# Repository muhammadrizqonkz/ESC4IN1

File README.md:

# ESC4IN1

Dokumentasi proyek capstone ESC 4-in-1: desain PCB, simulasi, dan pengujian motor.

## Isi repositori

| Folder | Isi |
| --- | --- |
| [PCBDesign](PCBDesign/) | Desain PCB KiCad dan model 3D |
| [Simulation](Simulation/) | Model dan hasil simulasi |
| [MotorTest](MotorTest/) | Foto pengukuran dan pengujian |

## PCBDesign

- [Skematik](PCBDesign/ESC_4in1.kicad_sch)
- [Layout PCB](PCBDesign/ESC_4in1.kicad_pcb)
- [Project KiCad](PCBDesign/ESC_4in1.kicad_pro)
- [Model 3D (STEP)](PCBDesign/ESC.step)
- [Render 3D](PCBDesign/ESC3D.png)

## Simulation

- [Model simulasi](Simulation/ModelSimulasi.png)
- [Hasil simulasi](Simulation/HasilSimulasi.jpeg)

## MotorTest

- [Pengukuran induktansi](MotorTest/InductanceMeasure.jpeg)
- [Pengukuran resistansi](MotorTest/ResistanceMeasure.jpeg)
- [Kamera termal ESC](MotorTest/ThermalCamESC.jpeg)

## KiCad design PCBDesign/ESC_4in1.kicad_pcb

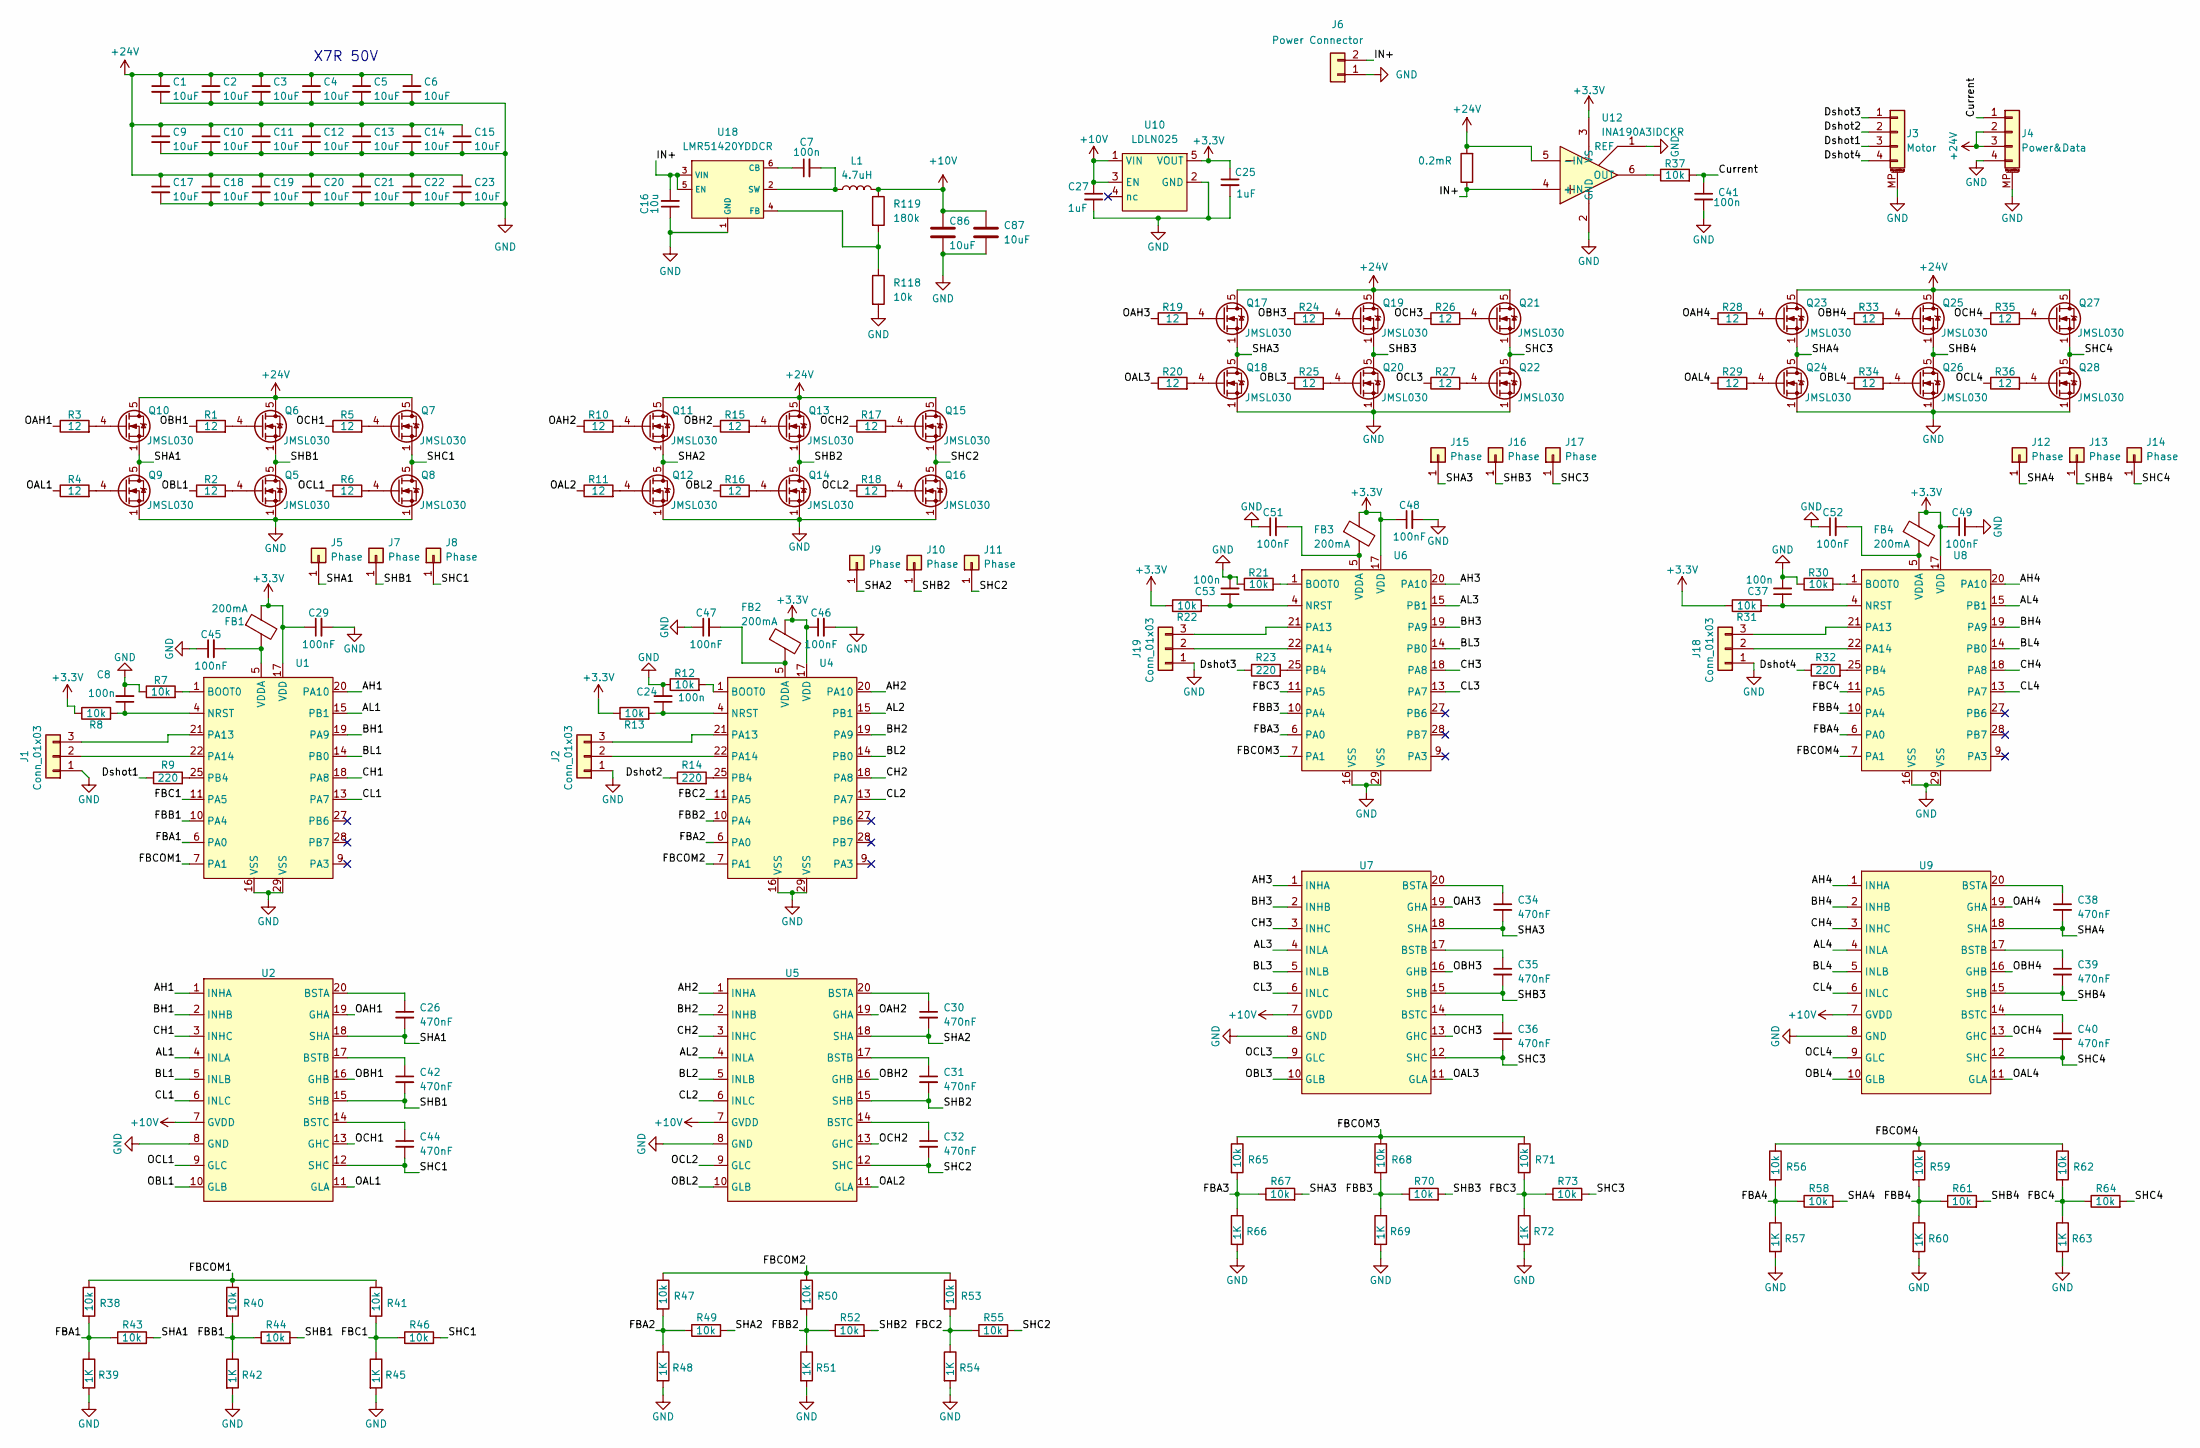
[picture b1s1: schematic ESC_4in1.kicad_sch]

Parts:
C1, C2, C3, C4, C5, C6, C9, C10, C11, C12, C13, C14, C15, C17, C18, C19, C20, C21, C22, C23: 10uF; C_1206_3216Metric_Pad1.33x1.80mm_HandSolder
C7: 100n; C_0603_1608Metric_Pad1.08x0.95mm_HandSolder
C8, C24, C37, C41, C53: 100n; C_0402_1005Metric_Pad0.74x0.62mm_HandSolder
C16: 10u; C_0603_1608Metric_Pad1.08x0.95mm_HandSolder
C25, C27: 1uF; C_0603_1608Metric_Pad1.08x0.95mm_HandSolder
C26, C30, C31, C32, C34, C35, C36, C38, C39, C40, C42, C44: 470nF; C_0603_1608Metric_Pad1.08x0.95mm_HandSolder
C29, C45, C46, C47, C48, C49, C51, C52: 100nF; C_01005_0402Metric_Pad0.57x0.30mm_HandSolder
C86, C87: 10uF; C_0603_1608Metric; LCSC C2762594
FB1, FB2, FB3, FB4: 200mA; R_0201_0603Metric_Pad0.64x0.40mm_HandSolder
J1, J2, J19: Conn_01x03; PinHeader_1x03_P2.54mm_Horizontal
J3: Motor; JST_SH_SM04B-SRSS-TB_1x04-1MP_P1.00mm_Horizontal
J4: Power&Data; JST_SH_SM04B-SRSS-TB_1x04-1MP_P1.00mm_Horizontal
J5, J7, J8, J9, J10, J11, J12, J13, J14, J15, J16, J17: Phase; motorterminal
J6: Power Connector; AMASS_XT30PW-M
J18: Conn_01x03; PinHeader_1x03_P2.54mm_Vertical_SMD_Pin1Left
L1: 4.7uH; SPM3012
Q5, Q6, Q7, Q8, Q9, Q10, Q11, Q12, Q13, Q14, Q15, Q16, Q17, Q18, Q19, Q20, Q21, Q22, Q23, Q24, Q25, Q26, Q27, Q28: JMSL030; Vishay_PowerPAK_1212-8_Single
R1, R2, R3, R4, R5, R6, R10, R11, R15, R16, R17, R18, R19, R20, R24, R25, R26, R27, R28, R29, R33, R34, R35, R36: 12; R_0603_1608Metric_Pad0.98x0.95mm_HandSolder
R7, R8, R12, R13, R21, R22, R30, R31, R38, R40, R41, R43, R44, R46, R47, R49, R50, R52, R53, R55, R56, R58, R59, R61, R62, R64, R65, R67, R68, R70, R71, R73: 10k; R_0603_1608Metric_Pad0.98x0.95mm_HandSolder
R9, R14, R23, R32: 220; R_0603_1608Metric_Pad0.98x0.95mm_HandSolder
R37: 10k; R_0402_1005Metric_Pad0.72x0.64mm_HandSolder
R39, R42, R45, R48, R51, R54, R57, R60, R63, R66, R69, R72: 1K; R_0603_1608Metric_Pad0.98x0.95mm_HandSolder
R118: 10k; R_0402_1005Metric_Pad0.72x0.64mm_HandSolder; LCSC C106225
R119: 180k; R_0402_1005Metric_Pad0.72x0.64mm_HandSolder; LCSC C423759
Rsense1: 0.2mR; R_2512_6332Metric; LCSC C695806
U1, U4, U6, U8: QFN-28-1EP_4x4mm_P0.4mm_EP2.4x2.4mm
U2, U5, U7, U9: TSSOP-20_4.4x6.5mm_P0.65mm
U10: LDLN025; SOT-23-5_HandSoldering
U12: INA190A3IDCKR; SOT-363_SC-70-6; LCSC C2058245
U18: LMR51420YDDCR; SOT-23-6_Handsoldering; LCSC C7296200

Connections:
+3.3V: C25.1, C29.1, C46.1, C48.1, C49.1, FB1.1, FB2.1, FB3.1, FB4.1, R8.1, R13.1, R22.1, R31.1, U1.17 (VDD), U4.17 (VDD), U6.17 (VDD), U8.17 (VDD), U10.5 (VOUT), U12.3 (VS)
+10V: C27.1, C86.1, C87.1, L1.1, R119.1, U2.7 (GVDD), U5.7 (GVDD), U7.7 (GVDD), U9.7 (GVDD), U10.1 (VIN), U10.3 (EN)
+24V: C1.1, C2.1, C3.1, C4.1, C5.1, C6.1, C9.1, C10.1, C11.1, C12.1, C13.1, C14.1, C15.1, C17.1, C18.1, C19.1, C20.1, C21.1, C22.1, C23.1, J4.2, J4.3, Q6.5 (D), Q7.5 (D), Q10.5 (D), Q11.5 (D), Q13.5 (D), Q15.5 (D), Q17.5 (D), Q19.5 (D), Q21.5 (D), Q23.5 (D), Q25.5 (D), Q27.5 (D), Rsense1.2, U12.5 (-IN)
/AH1: U1.20 (PA10), U2.1 (INHA)
/AH2: U4.20 (PA10), U5.1 (INHA)
/AH3: U6.20 (PA10), U7.1 (INHA)
/AH4: U8.20 (PA10), U9.1 (INHA)
/AL1: U1.15 (PB1), U2.4 (INLA)
/AL2: U4.15 (PB1), U5.4 (INLA)
/AL3: U6.15 (PB1), U7.4 (INLA)
/AL4: U8.15 (PB1), U9.4 (INLA)
/BH1: U1.19 (PA9), U2.2 (INHB)
/BH2: U4.19 (PA9), U5.2 (INHB)
/BH3: U6.19 (PA9), U7.2 (INHB)
/BH4: U8.19 (PA9), U9.2 (INHB)
/BL1: U1.14 (PB0), U2.5 (INLB)
/BL2: U4.14 (PB0), U5.5 (INLB)
/BL3: U6.14 (PB0), U7.5 (INLB)
/BL4: U8.14 (PB0), U9.5 (INLB)
/CH1: U1.18 (PA8), U2.3 (INHC)
/CH2: U4.18 (PA8), U5.3 (INHC)
/CH3: U6.18 (PA8), U7.3 (INHC)
/CH4: U8.18 (PA8), U9.3 (INHC)
/CL1: U1.13 (PA7), U2.6 (INLC)
/CL2: U4.13 (PA7), U5.6 (INLC)
/CL3: U6.13 (PA7), U7.6 (INLC)
/CL4: U8.13 (PA7), U9.6 (INLC)
/Current: C41.1, J4.1, R37.2
/Dshot1: J3.3, R9.1
/Dshot2: J3.2, R14.1
/Dshot3: J3.1, R23.1
/Dshot4: J3.4, R32.1
/FBA1: R38.2, R39.1, R43.1, U1.6 (PA0)
/FBA2: R47.2, R48.1, R49.1, U4.6 (PA0)
/FBA3: R65.2, R66.1, R67.1, U6.6 (PA0)
/FBA4: R56.2, R57.1, R58.1, U8.6 (PA0)
/FBB1: R40.2, R42.1, R44.1, U1.10 (PA4)
/FBB2: R50.2, R51.1, R52.1, U4.10 (PA4)
/FBB3: R68.2, R69.1, R70.1, U6.10 (PA4)
/FBB4: R59.2, R60.1, R61.1, U8.10 (PA4)
/FBC1: R41.2, R45.1, R46.1, U1.11 (PA5)
/FBC2: R53.2, R54.1, R55.1, U4.11 (PA5)
/FBC3: R71.2, R72.1, R73.1, U6.11 (PA5)
/FBC4: R62.2, R63.1, R64.1, U8.11 (PA5)
/FBCOM1: R38.1, R40.1, R41.1, U1.7 (PA1)
/FBCOM2: R47.1, R50.1, R53.1, U4.7 (PA1)
/FBCOM3: R65.1, R68.1, R71.1, U6.7 (PA1)
/FBCOM4: R56.1, R59.1, R62.1, U8.7 (PA1)
/IN+: C16.2, J6.2, Rsense1.1, U12.4 (+IN), U18.3 (VIN), U18.5 (EN)
/OAH1: R3.1, U2.19 (GHA)
/OAH2: R10.1, U5.19 (GHA)
/OAH3: R19.1, U7.19 (GHA)
/OAH4: R28.1, U9.19 (GHA)
/OAL1: R4.1, U2.11 (GLA)
/OAL2: R11.1, U5.11 (GLA)
/OAL3: R20.1, U7.11 (GLA)
/OAL4: R29.1, U9.11 (GLA)
/OBH1: R1.1, U2.16 (GHB)
/OBH2: R15.1, U5.16 (GHB)
/OBH3: R24.1, U7.16 (GHB)
/OBH4: R33.1, U9.16 (GHB)
/OBL1: R2.1, U2.10 (GLB)
/OBL2: R16.1, U5.10 (GLB)
/OBL3: R25.1, U7.10 (GLB)
/OBL4: R34.1, U9.10 (GLB)
/OCH1: R5.1, U2.13 (GHC)
/OCH2: R17.1, U5.13 (GHC)
/OCH3: R26.1, U7.13 (GHC)
/OCH4: R35.1, U9.13 (GHC)
/OCL1: R6.1, U2.9 (GLC)
/OCL2: R18.1, U5.9 (GLC)
/OCL3: R27.1, U7.9 (GLC)
/OCL4: R36.1, U9.9 (GLC)
/SHA1: C26.2, J5.1 (Pin_1_1), Q9.5 (D), Q10.1 (S), Q10.2 (S), Q10.3 (S), R43.2, U2.18 (SHA)
/SHA2: C30.2, J9.1 (Pin_1_1), Q11.1 (S), Q11.2 (S), Q11.3 (S), Q12.5 (D), R49.2, U5.18 (SHA)
/SHA3: C34.2, J15.1 (Pin_1_1), Q17.1 (S), Q17.2 (S), Q17.3 (S), Q18.5 (D), R67.2, U7.18 (SHA)
/SHA4: C38.2, J12.1 (Pin_1_1), Q23.1 (S), Q23.2 (S), Q23.3 (S), Q24.5 (D), R58.2, U9.18 (SHA); also elsewhere on the board
/SHB1: C42.2, J7.1 (Pin_1_1), Q5.5 (D), Q6.1 (S), Q6.2 (S), Q6.3 (S), R44.2, U2.15 (SHB)
/SHB2: C31.2, J10.1 (Pin_1_1), Q13.1 (S), Q13.2 (S), Q13.3 (S), Q14.5 (D), R52.2, U5.15 (SHB)
/SHB3: C35.2, J16.1 (Pin_1_1), Q19.1 (S), Q19.2 (S), Q19.3 (S), Q20.5 (D), R70.2, U7.15 (SHB)
/SHB4: C39.2, J13.1 (Pin_1_1), Q25.1 (S), Q25.2 (S), Q25.3 (S), Q26.5 (D), R61.2, U9.15 (SHB)
/SHC1: C44.2, J8.1 (Pin_1_1), Q7.1 (S), Q7.2 (S), Q7.3 (S), Q8.5 (D), R46.2, U2.12 (SHC)
/SHC2: C32.2, J11.1 (Pin_1_1), Q15.1 (S), Q15.2 (S), Q15.3 (S), Q16.5 (D), R55.2, U5.12 (SHC)
/SHC3: C36.2, J17.1 (Pin_1_1), Q21.1 (S), Q21.2 (S), Q21.3 (S), Q22.5 (D), R73.2, U7.12 (SHC)
/SHC4: C40.2, J14.1 (Pin_1_1), Q27.1 (S), Q27.2 (S), Q27.3 (S), Q28.5 (D), R64.2, U9.12 (SHC)
GND: C1.2, C2.2, C3.2, C4.2, C5.2, C6.2, C8.2, C9.2, C10.2, C11.2, C12.2, C13.2, C14.2, C15.2, C16.1, C17.2, C18.2, C19.2, C20.2, C21.2, C22.2, C23.2, C24.2, C25.2, C27.2, C29.2, C37.2, C41.2, C45.1, C46.2, C47.1, C48.2, C49.2, C51.1, C52.1, C53.2, C86.2, C87.2, J1.1, J2.1, J3.MP (MountPin), J4.4, J4.MP (MountPin), J6.1, J18.1, J19.1, Q5.1 (S), Q5.2 (S), Q5.3 (S), Q8.1 (S), Q8.2 (S), Q8.3 (S), Q9.1 (S), Q9.2 (S), Q9.3 (S), Q12.1 (S), Q12.2 (S), Q12.3 (S), Q14.1 (S), Q14.2 (S), Q14.3 (S), Q16.1 (S), Q16.2 (S), Q16.3 (S), Q18.1 (S), Q18.2 (S), Q18.3 (S), Q20.1 (S), Q20.2 (S), Q20.3 (S), Q22.1 (S), Q22.2 (S), Q22.3 (S), Q24.1 (S), Q24.2 (S), Q24.3 (S), Q26.1 (S), Q26.2 (S), Q26.3 (S), Q28.1 (S), Q28.2 (S), Q28.3 (S), R7.1, R12.1, R21.1, R30.1, R39.2, R42.2, R45.2, R48.2, R51.2, R54.2, R57.2, R60.2, R63.2, R66.2, R69.2, R72.2, R118.2, U1.16 (VSS), U1.29 (VSS), U2.8 (GND), U4.16 (VSS), U4.29 (VSS), U5.8 (GND), U6.16 (VSS), U6.29 (VSS), U7.8 (GND), U8.16 (VSS), U8.29 (VSS), U9.8 (GND), U10.2 (GND), U12.1 (REF), U12.2 (GND), U18.1 (GND)
unnamed: J1.2, U1.22 (PA14)
unnamed: J1.3, U1.21 (PA13)
unnamed: J2.2, U4.22 (PA14)
unnamed: J2.3, U4.21 (PA13)
unnamed: J18.2, U8.22 (PA14)
unnamed: J18.3, U8.21 (PA13)
unnamed: J19.2, U6.22 (PA14)
unnamed: J19.3, U6.21 (PA13)
unnamed: Q5.4 (G), R2.2
unnamed: Q6.4 (G), R1.2
unnamed: Q7.4 (G), R5.2
unnamed: Q8.4 (G), R6.2
unnamed: Q9.4 (G), R4.2
unnamed: Q10.4 (G), R3.2
unnamed: Q11.4 (G), R10.2
unnamed: Q12.4 (G), R11.2
unnamed: Q13.4 (G), R15.2
unnamed: Q14.4 (G), R16.2
unnamed: Q15.4 (G), R17.2
unnamed: Q16.4 (G), R18.2
unnamed: Q17.4 (G), R19.2
unnamed: Q18.4 (G), R20.2
unnamed: Q19.4 (G), R24.2
unnamed: Q20.4 (G), R25.2
unnamed: Q21.4 (G), R26.2
unnamed: Q22.4 (G), R27.2
unnamed: Q23.4 (G), R28.2
unnamed: Q24.4 (G), R29.2
unnamed: Q25.4 (G), R33.2
unnamed: Q26.4 (G), R34.2
unnamed: Q27.4 (G), R35.2
unnamed: Q28.4 (G), R36.2
unnamed: R7.2, U1.1 (BOOT0)
unnamed: C8.1, R8.2, U1.4 (NRST)
unnamed: R9.2, U1.25 (PB4)
unnamed: C45.2, FB1.2, U1.5 (VDDA)
unnamed: C26.1, U2.20 (BSTA)
unnamed: C42.1, U2.17 (BSTB)
unnamed: C44.1, U2.14 (BSTC)
unnamed: R12.2, U4.1 (BOOT0)
unnamed: C24.1, R13.2, U4.4 (NRST)
unnamed: R14.2, U4.25 (PB4)
unnamed: C47.2, FB2.2, U4.5 (VDDA)
unnamed: C30.1, U5.20 (BSTA)
unnamed: C31.1, U5.17 (BSTB)
unnamed: C32.1, U5.14 (BSTC)
unnamed: R21.2, U6.1 (BOOT0)
unnamed: C53.1, R22.2, U6.4 (NRST)
unnamed: R23.2, U6.25 (PB4)
unnamed: C51.2, FB3.2, U6.5 (VDDA)
unnamed: C34.1, U7.20 (BSTA)
unnamed: C35.1, U7.17 (BSTB)
unnamed: C36.1, U7.14 (BSTC)
unnamed: R30.2, U8.1 (BOOT0)
unnamed: C37.1, R31.2, U8.4 (NRST)
unnamed: R32.2, U8.25 (PB4)
unnamed: C52.2, FB4.2, U8.5 (VDDA)
unnamed 143: C38.1, U9.20 (BSTA); also elsewhere on the board
unnamed: C39.1, U9.17 (BSTB)
unnamed: C40.1, U9.14 (BSTC)
unnamed: R37.1, U12.6 (OUT)
unnamed: C7.1, U18.6 (CB)
unnamed: R118.1, R119.2, U18.4 (FB)
unnamed: C7.2, L1.2, U18.2 (SW)

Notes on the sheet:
X7R 50V

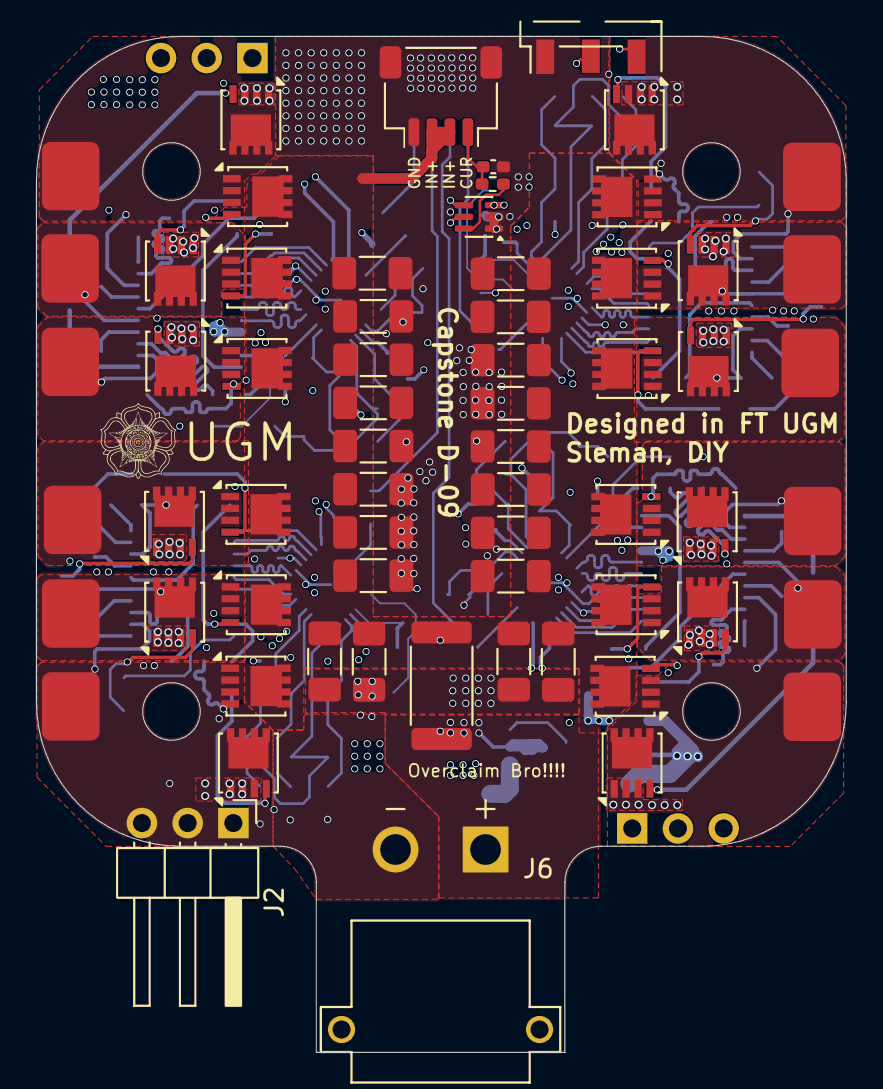
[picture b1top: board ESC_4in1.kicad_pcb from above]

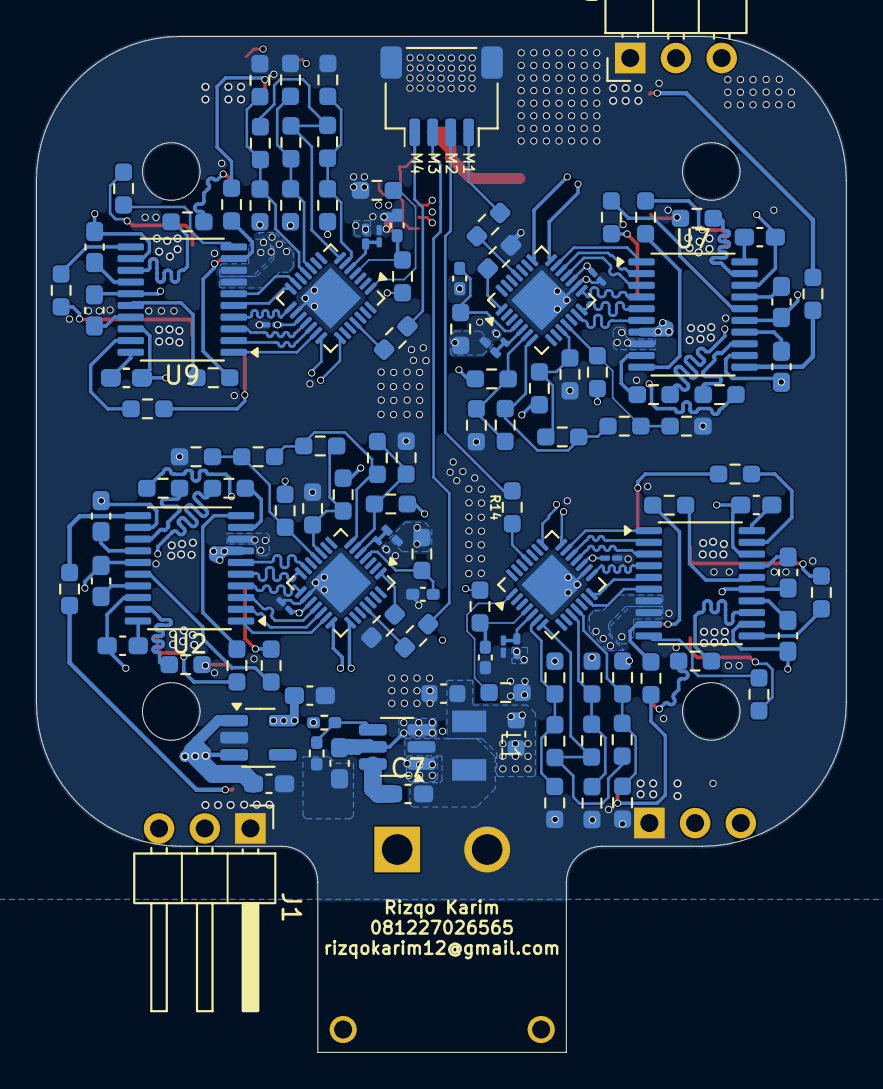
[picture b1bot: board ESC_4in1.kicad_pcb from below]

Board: 4 copper layers, 45.0 x 56.4 mm, 187 parts (123 on the bottom side), 150 nets.

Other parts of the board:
C30#2: 470nF; C_0603_1608Metric_Pad1.08x0.95mm_HandSolder

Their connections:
/SHA4: C30#2.2; also elsewhere on the board
unnamed 143: C30#2.1; also elsewhere on the board
